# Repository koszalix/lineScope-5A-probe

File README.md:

# lineScope 5A  probe

This repo contains PCB files for lineScope 5A probe, 
full project documentation is available [here](https://github.com/koszalix/lineScope)

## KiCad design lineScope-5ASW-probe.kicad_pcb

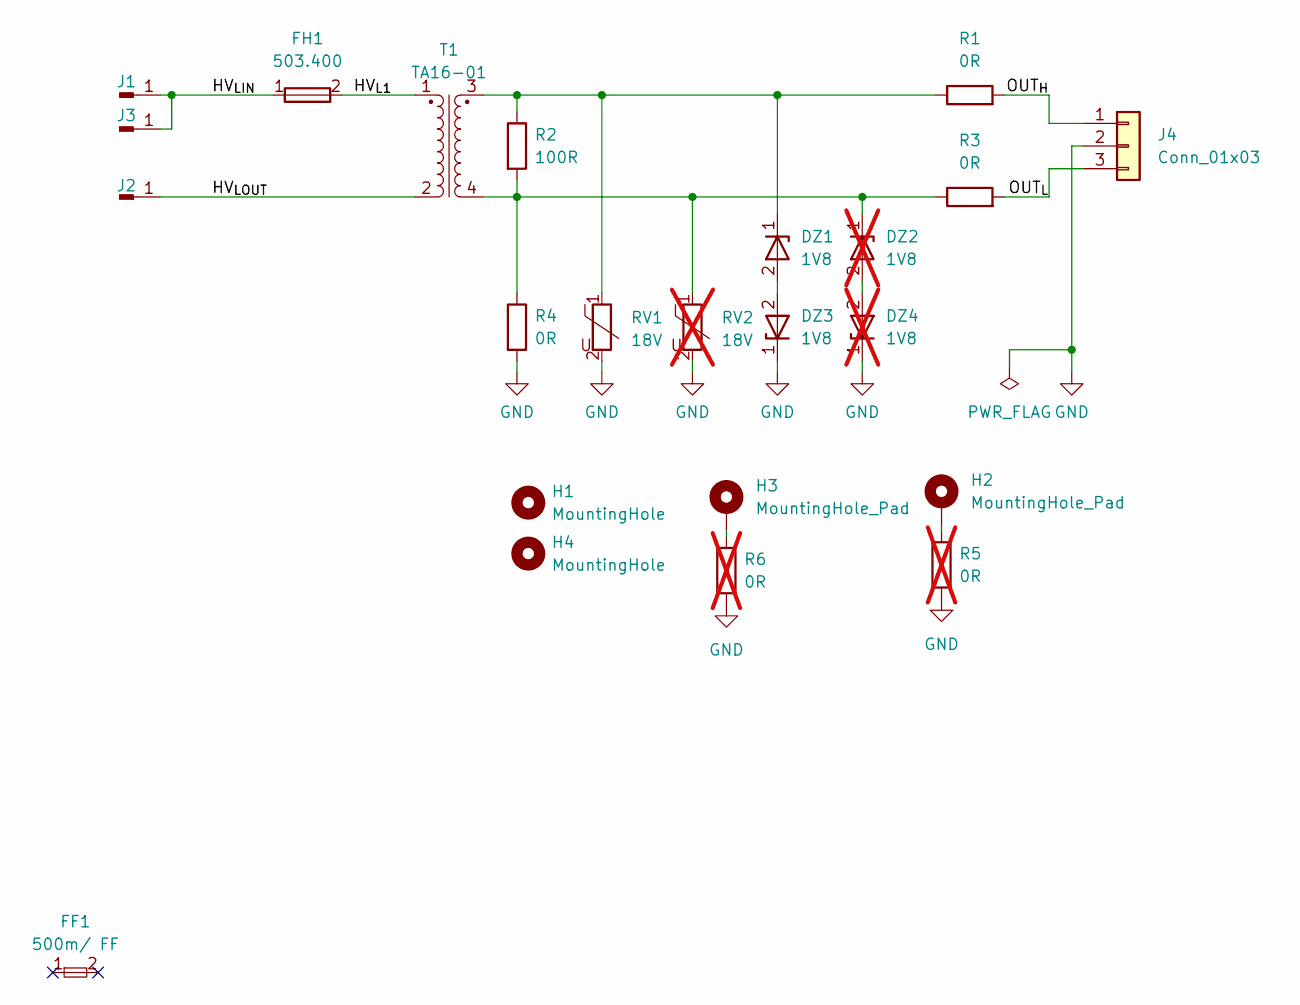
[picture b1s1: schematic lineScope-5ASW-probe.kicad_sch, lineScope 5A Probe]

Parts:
DZ1, DZ3: 1V8; D_SOD-123; MPN MMSZ4678T1G
DZ2, DZ4: 1V8; D_SOD-123; MPN MMSZ4678T1G; not fitted
FF1: 500m/ FF; MPN 7000140.5
FH1: 503.400; ESKA_503.400; MPN 503.400
H1, H4: MountingHole; MountingHole_3.2mm_M3
H2, H3: MountingHole_Pad; MountingHole_3.2mm_M3_Pad
J1, J2, J3: TE-1-726388-2; MPN TE-1-726388-2
J4: Conn_01x03; PinHeader_1x03_P2.54mm_Horizontal
R1, R3: 0R; R_1206_3216Metric_Pad1.30x1.75mm_HandSolder
R2: 100R; R_0603_1608Metric; Tolerance 1%; MPN RC0603FR-07100R
R4: 0R; R_0603_1608Metric; Tolerance 1%; MPN RC0603FR-070R
R5, R6: 0R; R_0603_1608Metric; Tolerance 1%; MPN RC0603FR-070R; not fitted
RV1: 18V; R_0603_1608Metric_Pad0.98x0.95mm_HandSolder; MPN MCVZ0603M180AGT
RV2: 18V; R_0603_1608Metric_Pad0.98x0.95mm_HandSolder; MPN MCVZ0603M180AGT; not fitted
T1: TA16-01; PowerUC-TV16

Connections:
/HV_{L1}: FH1.2, T1.1
/HV_{LIN}: FH1.1, J1.1, J3.1
/HV_{LOUT}: J2.1, T1.2
/OUT_{H}: J4.1, R1.2
/OUT_{L}: J4.3, R3.2
GND: DZ3.1, DZ4.1, J4.2, R4.2, R5.2, R6.2, RV1.2, RV2.2
unnamed: DZ1.1, R1.1, R2.1, RV1.1, T1.3
unnamed: DZ1.2, DZ3.2
unnamed: DZ2.1, R2.2, R3.1, R4.1, RV2.1, T1.4
unnamed: DZ2.2, DZ4.2
unnamed: H2.1, R5.1
unnamed: H3.1, R6.1

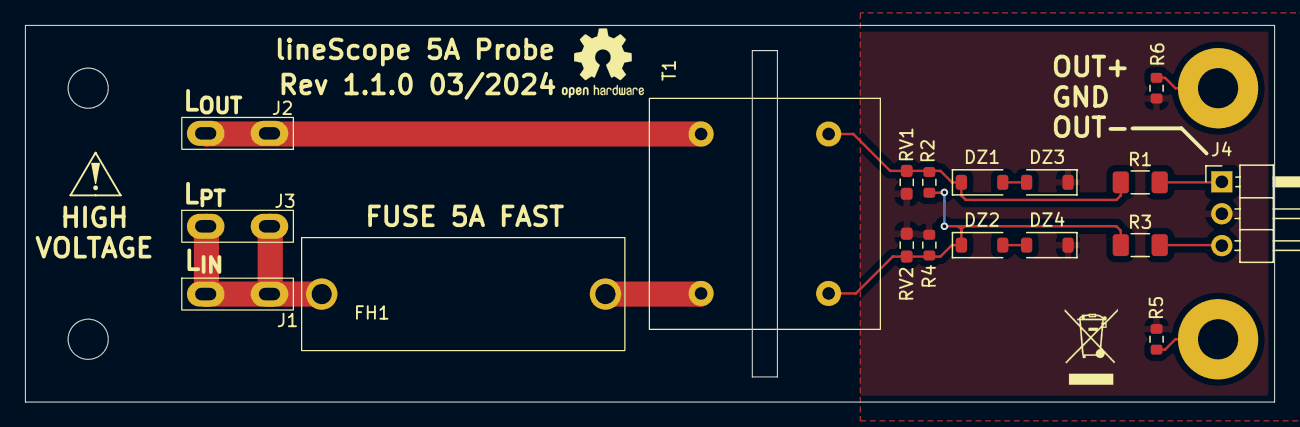
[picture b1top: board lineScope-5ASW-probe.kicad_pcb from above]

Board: 2 copper layers, 99.5 x 30.0 mm, 22 parts (0 on the bottom side), 12 nets.

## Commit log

2024-03-20 Create schematic file
    Route PCB
2024-03-20 Add gitignore
2024-03-21 Minor fixes
2024-04-21 Minor update
2024-05-26 Change R2 to 100Ohm
2024-05-26 Bump revsion to 1.1.0
